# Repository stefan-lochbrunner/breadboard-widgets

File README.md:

A collection of widgets/adapters/breakouts to make prototyping easier.
For more infos please see [**project page on HaD.io**](https://hackaday.io/project/6332-breadboard-widgets). A panel with a subset of these booards can also be ordered from the [**DirtyPCBs store**](http://dirtypcbs.com/view.php?share=9791&accesskey=ab0e86ffb8323f031e5f15a2c98e4056)

#### ATtiny prog board
Programming board suitable for ATtiny45/85 microcontrollers. Plugs into a breadboards power rails to minimize required space.
USB version pin compatible with uUSB breakout.
[**more info**](https://hackaday.io/project/6332-breadboard-widgets/log/19613-attiny-prog-board)

##### Standard:

##### With USB:

#### DBx breakout
Simple breakout for DA-15, DB/DE-9 & DE-15(VGA) connectors. DB-9 to be placed on DA-15 footprint. [**more info**](https://hackaday.io/project/6332/log/26554)

#### ISP breakout
Simple ISP breakout. Order of pins corresponds to ATmega328 DIP so breakout can be plugged in next to it. Jumper wire required for RST. Also fits ATtiny45/85 with additional jumper for GND.
[**more info**](https://hackaday.io/project/6332-breadboard-widgets/log/19660-isp-breakout)

##### v1.2

Added two additional pins to ISP & breadboard headers to allow this board to be used as breakout for e.g. ESP-01's.

#### MOSFET breakout
DPAK MOSFET breakout to be used as single channel PWM driver. Footprint should also fit SOT-223 package where pin 2 is internally connected to tab.
[**more info**](https://hackaday.io/project/6332-breadboard-widgets/log/21781-mosfet-breakout-for-pwm-driver)

#### SMD LED breakout
Straight forward SMD LED breakout. See also [**revised button board that can be used as LED breakout**](https://github.com/stefan-lochbrunner/breadboard-widgets/tree/master/button)

##### single

##### multi

#### SOIC/TSSOP-16 breakout & protoboard
Some variations on a SOIC-16 and TSSOP-16 breakout board.

#### USB breakouts

##### uUSB breakout
Main functionality is to provide "VUSB circuitry" for AVR microcontrollers. Can also be used as generic uUSB breakout by shorting 68R resistor footprints or as breadboard power supply (supplying 5V).
[**more info**](https://hackaday.io/project/6332-breadboard-widgets/log/19615-uusb-breakout)

###### v1

###### v2
Allows for supplying different voltages by populating the bottom side with desired regulator. For 5V short solder jumper.

superseded by v3

###### v3
Allows for supplying different voltages by populating the bottom side with desired regulator. The following modes are possible:

- Supply rail and Vcc pin with 5V directly from USB (regulator not populated, short all 3 pads of solder jumper)
- Supply regulator with 5V from USB which in turn supplies rail and Vcc pin (short center and top pad)
- Supply regulator from rail and get regulated voltage on Vcc pin (short center and bottom pad)

##### USB-B

#### Audio breakouts
Breakout boards for 3.5mm TRS & RCA jacks. [**more info**](https://hackaday.io/project/6332-breadboard-widgets/log/21029-sufs-audio-breakouts)

Based on @sufzoli 's https://github.com/sufzoli/suf-electronics-breadboard

Combined both into single board to save PCB space.

#### Button w/ pull resistor
[**more info**](https://hackaday.io/project/6332-breadboard-widgets/log/19614-button-w-pull-updown)

##### single button
Small board that incorporates a button and pull-resistor. Can be plugged into power rails. Depending on which side of a breadboard it is plugged in, acts as pull-up or pull-down. Optional footprints for low-pass filter for debouncing.

##### single button with SMD LED breakout
added over complicated LED breakout to utilize board space. Also added arrow to indicate pull direction.

#### Negative voltage converter
Included files of @sufzoli 's [**voltage inverter**](https://github.com/sufzoli/suf-electronics-USB-INV-PM) here and remade in Eagle for coherency. [**more info**](https://hackaday.io/project/6332-breadboard-widgets/log/22127-sufs-negative-voltage-converter)

Based on ICL7660, inverts supply voltage.

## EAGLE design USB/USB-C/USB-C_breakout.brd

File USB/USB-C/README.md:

# USB 2.0 Type C breakout
-------------------------

USB-C breakout inspired by the [Adafruit USB Type C Breakout Board](https://github.com/adafruit/Adafruit-USB-C-Downstream-Breakout) with [breadboard power rail connector](https://hackaday.io/project/6332-breadboard-widgets/log/19631-pwr-thingy) and power indicator LED.

<br>

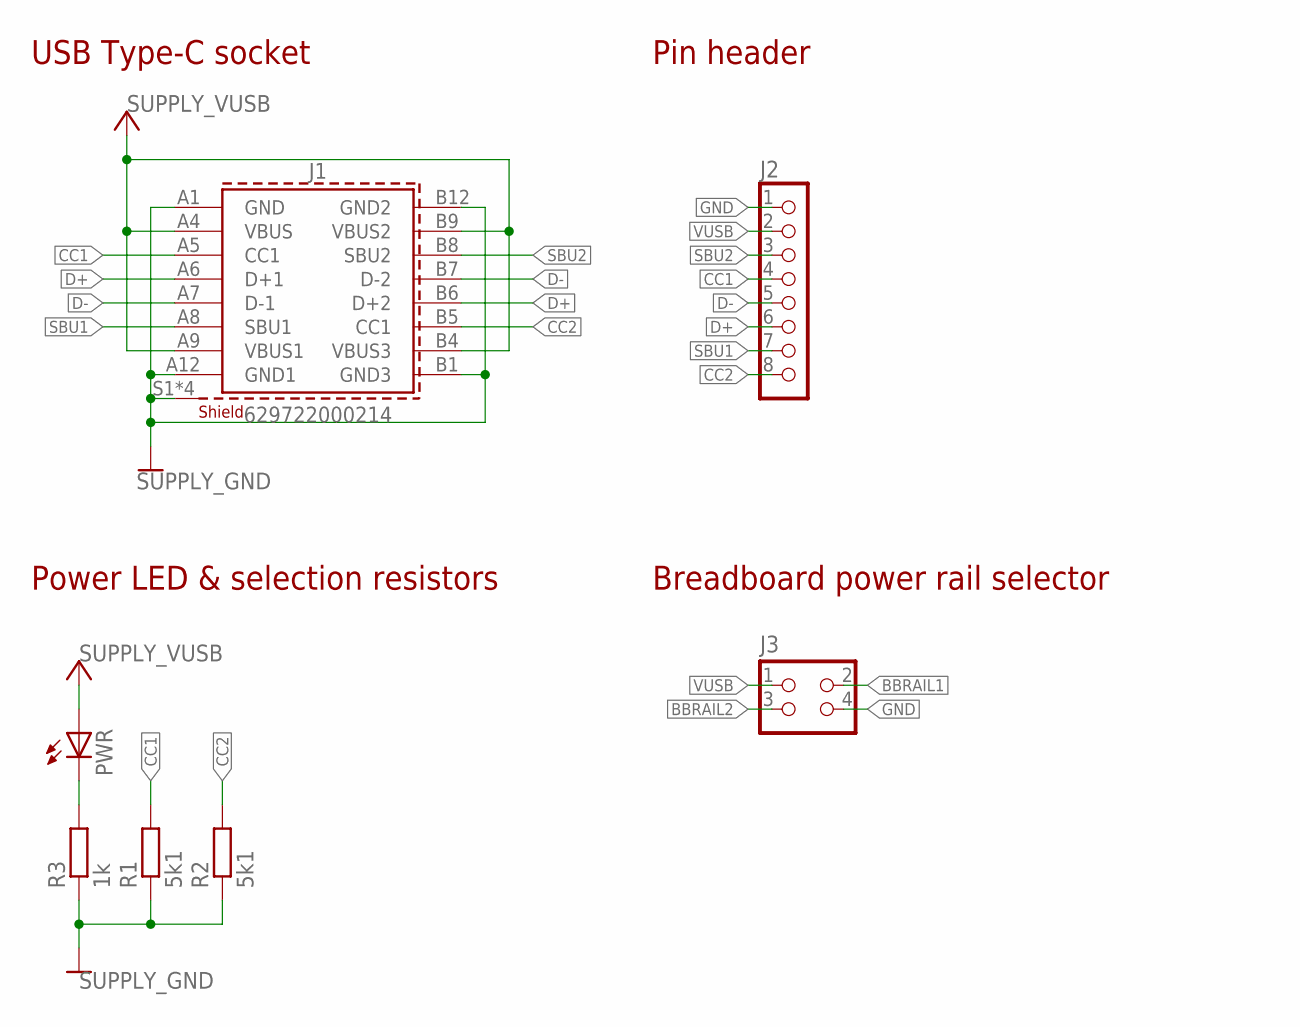
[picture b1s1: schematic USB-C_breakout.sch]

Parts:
J1: 629722000214
J2: CON_HEADER_1X08-PTH; M1X8
J3: CON_HEADER_2X02-PTH; M2X2
PWR: LED-0603; LED-603
R1, R2: 5k1; R603
R3: 1k; R603

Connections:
BBRAIL1: J3.2
BBRAIL2: J3.3
CC1: J1.A5 (CC1), J2.4, R1.2
CC2: J1.B5 (CC1), J2.8, R2.2
D+: J1.A6 (D+1), J1.B6 (D+2), J2.6
D-: J1.A7 (D-1), J1.B7 (D-2), J2.5
GND: J1.A1 (GND), J1.A12 (GND1), J1.B1 (GND3), J1.B12 (GND2), J1.S1 (SHIELD), J1.S2 (SHIELD), J1.S3 (SHIELD), J1.S4 (SHIELD), J2.1, J3.4, R1.1, R2.1, R3.1
unnamed: PWR.C, R3.2
SBU1: J1.A8 (SBU1), J2.7
SBU2: J1.B8 (SBU2), J2.3
VUSB: J1.A4 (VBUS), J1.A9 (VBUS1), J1.B4 (VBUS3), J1.B9 (VBUS2), J2.2, J3.1, PWR.A

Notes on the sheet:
USB Type-C socket
Pin header
Power LED & selection resistors
Breadboard power rail selector

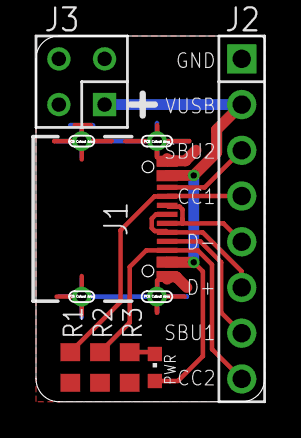
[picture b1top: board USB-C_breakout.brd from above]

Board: 2 copper layers, 12.7 x 20.3 mm, 7 parts (0 on the bottom side), 9 nets.

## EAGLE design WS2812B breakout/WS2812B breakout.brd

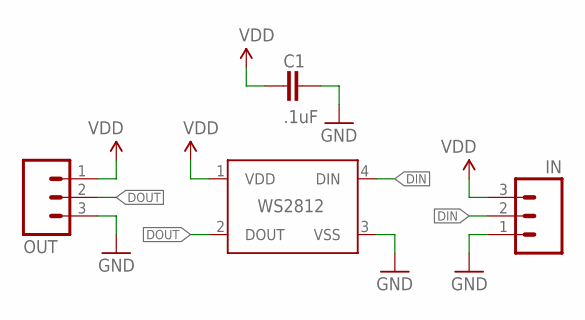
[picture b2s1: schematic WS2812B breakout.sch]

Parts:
C1: .1uF; C805
IN: CONN_03LOCK; 1X03_LOCK
OUT: CONN_03LOCK; 1X03_LOCK
WS2812: WS2812B

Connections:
DIN: IN.2, WS2812.4 (DIN)
DOUT: OUT.2, WS2812.2 (DOUT)
GND: C1.2, IN.1, OUT.3, WS2812.3 (VSS)
VDD: C1.1, IN.3, OUT.1, WS2812.1 (VDD)

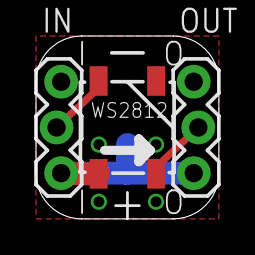
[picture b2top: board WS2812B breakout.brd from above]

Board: 2 copper layers, 10.2 x 10.2 mm, 4 parts (1 on the bottom side), 4 nets.

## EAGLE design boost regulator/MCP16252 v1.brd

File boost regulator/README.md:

Boost regulator board first designed by [**@sufzoli**](https://github.com/sufzoli), based on the [**Microchip MCP16252**](http://www.microchip.com/wwwproducts/en/MCP16252). [**more info**](https://hackaday.io/project/6332-breadboard-widgets/log/)

Set/remove jumper to output 3.3V/5V respectively.

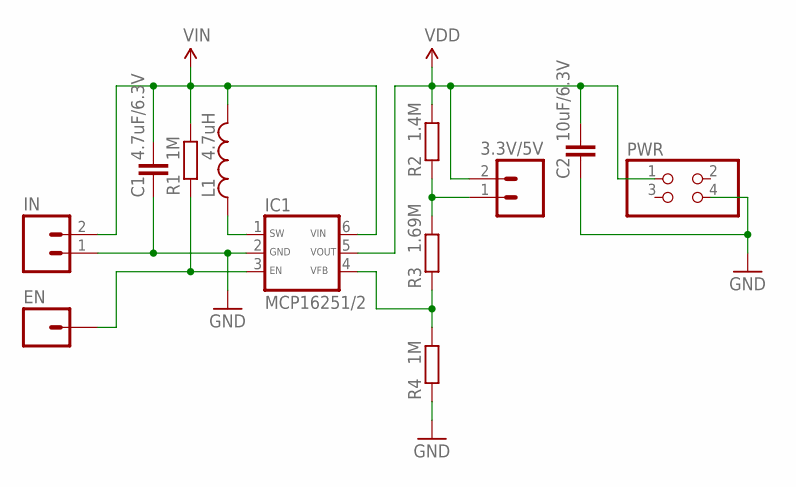
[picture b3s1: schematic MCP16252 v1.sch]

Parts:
3.3V/5V: M02PTH; 1X02
C1: 4.7uF/6.3V; C805
C2: 10uF/6.3V; C805
EN: M01PTH; 1X01
IC1: MCP16251/2; SOT-23-6
IN: M02PTH; 1X02
L1: 4.7uH; 1007
PWR: PINHD-2X2; 2X02
R1, R4: 1M; R603
R2: 1.4M; R603
R3: 1.69M; R603

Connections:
EN: EN.1, IC1.3 (EN), R1.1
GND: C1.2, C2.2, IC1.2 (GND), IN.1, PWR.4, R4.1
unnamed: IC1.1 (SW), L1.1
unnamed: IC1.4 (VFB), R3.1, R4.2
unnamed: 3.3V/5V.1, R2.1, R3.2
VDD: 3.3V/5V.2, C2.1, IC1.5 (VOUT), PWR.1, R2.2
VIN: C1.1, IC1.6 (VIN), IN.2, L1.2, R1.2

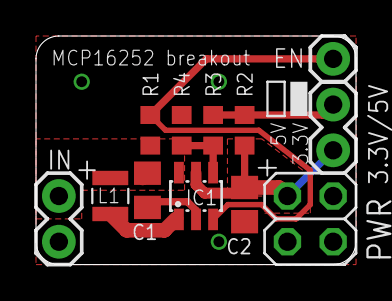
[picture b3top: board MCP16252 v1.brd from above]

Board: 2 copper layers, 17.8 x 12.7 mm, 12 parts (0 on the bottom side), 7 nets.

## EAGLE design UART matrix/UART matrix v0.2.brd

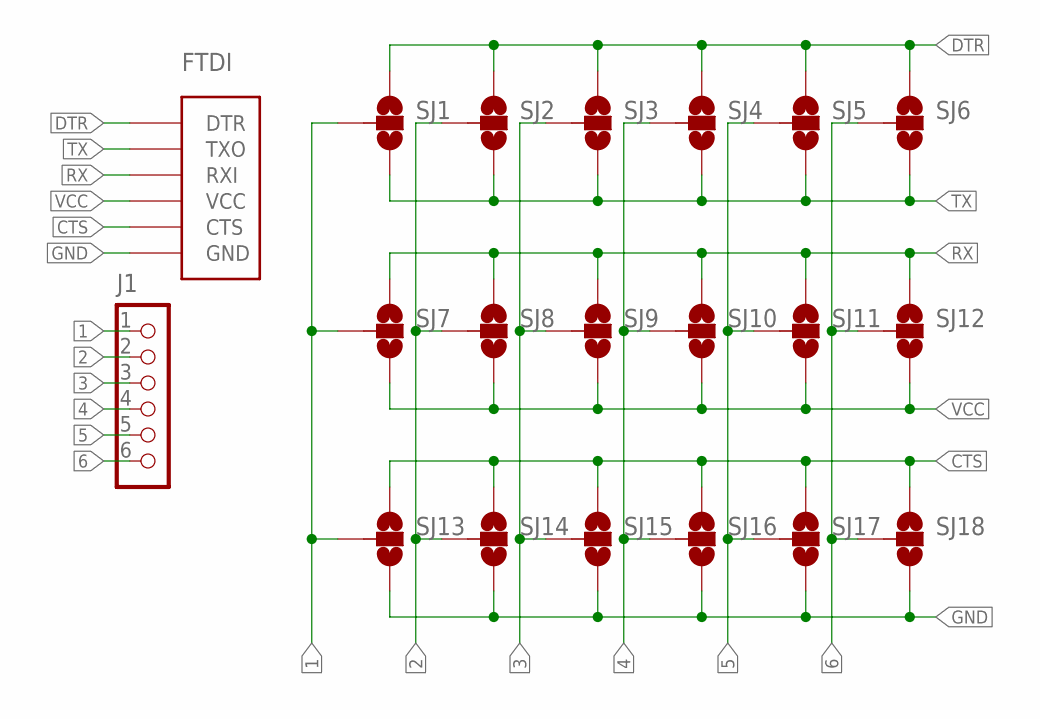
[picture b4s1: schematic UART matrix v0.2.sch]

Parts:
FTDI: FTDI_DEVICE; FTDI_DEVICE_SIDE
J1: CON_HEADER_1X06-PTH; M1X6
SJ1, SJ2, SJ3, SJ4, SJ5, SJ6, SJ7, SJ8, SJ9, SJ10, SJ11, SJ12, SJ13, SJ14, SJ15, SJ16, SJ17, SJ18: SOLDERJUMPER_2WAYT; SJ_2

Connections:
1: J1.1, SJ1.2, SJ7.2, SJ13.2
2: J1.2, SJ2.2, SJ8.2, SJ14.2
3: J1.3, SJ3.2, SJ9.2, SJ15.2
4: J1.4, SJ4.2, SJ10.2, SJ16.2
5: J1.5, SJ5.2, SJ11.2, SJ17.2
6: J1.6, SJ6.2, SJ12.2, SJ18.2
CTS: FTDI.P$5 (CTS), SJ13.1, SJ14.1, SJ15.1, SJ16.1, SJ17.1, SJ18.1
DTR: FTDI.P$1 (DTR), SJ1.1, SJ2.1, SJ3.1, SJ4.1, SJ5.1, SJ6.1
GND: FTDI.P$6 (GND), SJ13.3, SJ14.3, SJ15.3, SJ16.3, SJ17.3, SJ18.3
RX: FTDI.P$3 (RXI), SJ7.1, SJ8.1, SJ9.1, SJ10.1, SJ11.1, SJ12.1
TX: FTDI.P$2 (TXO), SJ1.3, SJ2.3, SJ3.3, SJ4.3, SJ5.3, SJ6.3
VCC: FTDI.P$4 (VCC), SJ7.3, SJ8.3, SJ9.3, SJ10.3, SJ11.3, SJ12.3

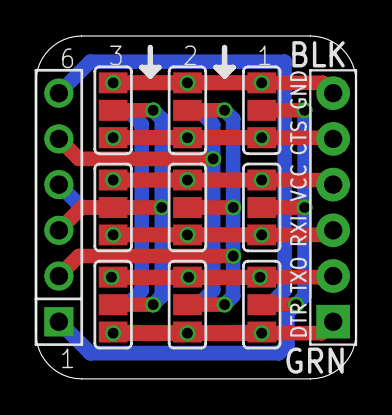
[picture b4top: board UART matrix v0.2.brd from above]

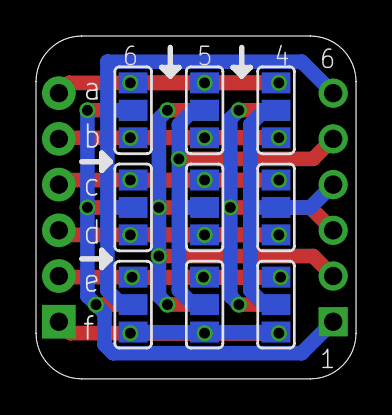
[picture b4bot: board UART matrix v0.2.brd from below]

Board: 2 copper layers, 17.8 x 19.1 mm, 20 parts (9 on the bottom side), 12 nets.

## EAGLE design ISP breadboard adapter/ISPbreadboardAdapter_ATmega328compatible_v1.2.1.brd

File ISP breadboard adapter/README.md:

Simple ISP breakout. Order of pins corresponds to ATmega328 DIP so breakout can be plugged in next to it. Jumper wire required for RST. Also fits ATtiny45/85 with additional jumper for GND.
[**more info**](https://hackaday.io/project/6332-breadboard-widgets/log/19660-isp-breakout)

**v1**

**v1.1**

**v1.2**

Added two additional pins to ISP & breadboard headers to allow this board to be used as breakout for e.g. ESP-01's.

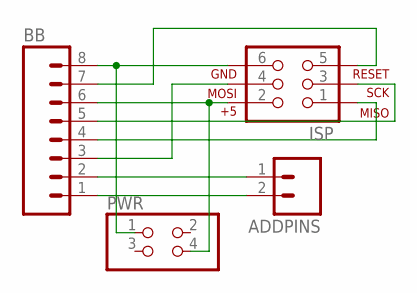
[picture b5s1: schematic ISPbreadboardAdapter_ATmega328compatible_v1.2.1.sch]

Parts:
ADDPINS: M02PTH; 1X02
BB: M08; 1X08_ROUND
ISP: AVR_SPI_PRG_6PTH; 2X3
PWR: PINHD-2X2; 2X02

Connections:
GND: BB.8, ISP.6, PWR.1
MISO: BB.4, ISP.1
MOSI: BB.3, ISP.4
unnamed: ADDPINS.1, BB.2
unnamed: ADDPINS.2, BB.1
RST: BB.7, ISP.5
SCK: BB.5, ISP.3
VCC: BB.6, ISP.2, PWR.4

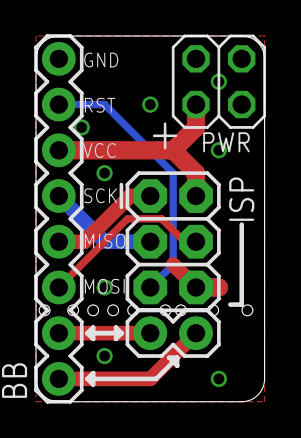
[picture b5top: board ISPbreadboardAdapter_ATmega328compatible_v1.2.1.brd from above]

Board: 2 copper layers, 12.7 x 20.3 mm, 4 parts (0 on the bottom side), 8 nets.

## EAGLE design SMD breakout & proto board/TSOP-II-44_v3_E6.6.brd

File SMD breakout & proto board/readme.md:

Some variations of SOIC/TSSOP-16 and -20 breakouts. [**more info**](https://hackaday.io/project/6332/log/26748)

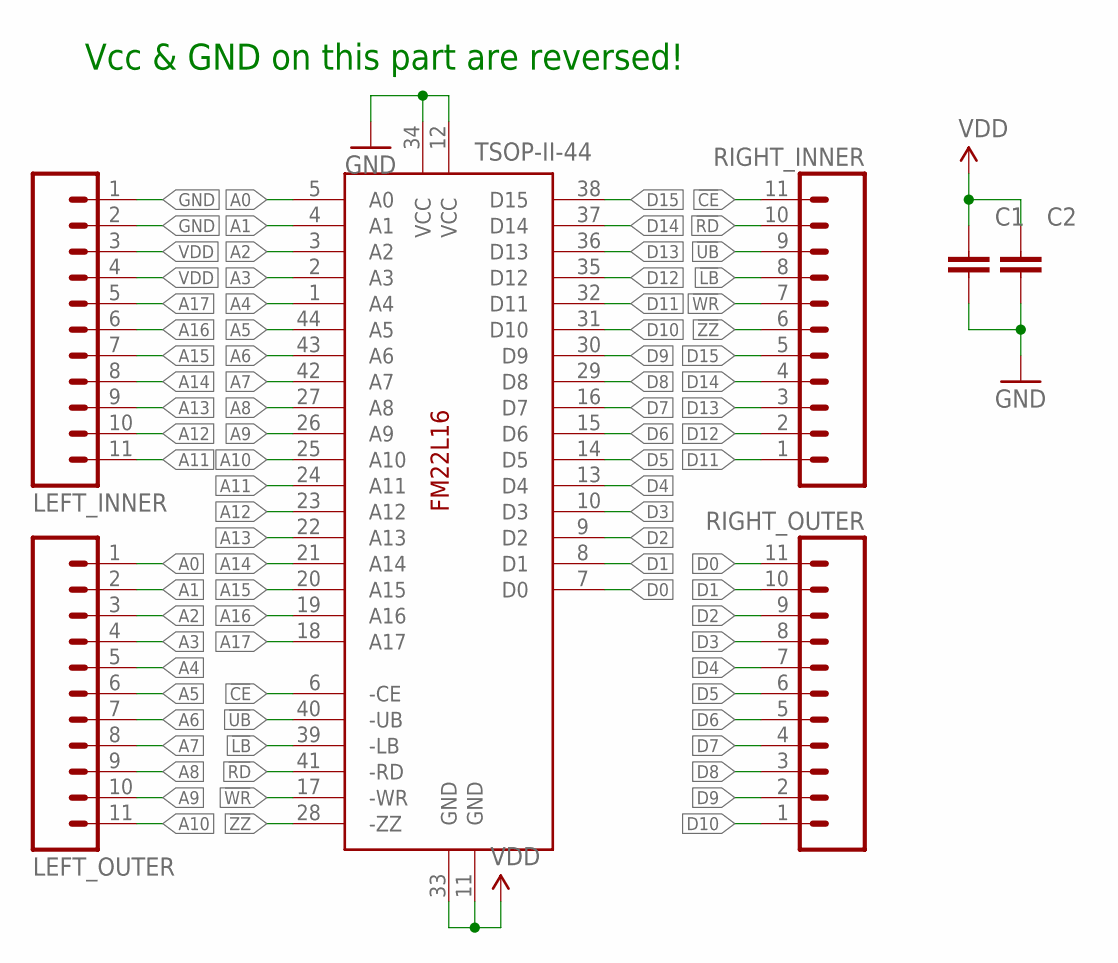
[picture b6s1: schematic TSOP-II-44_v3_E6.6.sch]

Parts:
C1, C2: CAPACITOR_NPOL-0603; C603
LEFT_INNER: M11PTH; 1X11
LEFT_OUTER: M11PTH; 1X11
RIGHT_INNER: M11PTH; 1X11
RIGHT_OUTER: M11PTH; 1X11
TSOP-II-44: FM22L16-TG; TSOPII-44

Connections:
!CE: RIGHT_INNER.11, TSOP-II-44.6 (-CE)
!LB: RIGHT_INNER.8, TSOP-II-44.39 (-LB)
!RD: RIGHT_INNER.10, TSOP-II-44.41 (-RD)
!UB: RIGHT_INNER.9, TSOP-II-44.40 (-UB)
!WR: RIGHT_INNER.7, TSOP-II-44.17 (-WR)
!ZZ: RIGHT_INNER.6, TSOP-II-44.28 (-ZZ)
A0: LEFT_OUTER.1, TSOP-II-44.5 (A0)
A1: LEFT_OUTER.2, TSOP-II-44.4 (A1)
A2: LEFT_OUTER.3, TSOP-II-44.3 (A2)
A3: LEFT_OUTER.4, TSOP-II-44.2 (A3)
A4: LEFT_OUTER.5, TSOP-II-44.1 (A4)
A5: LEFT_OUTER.6, TSOP-II-44.44 (A5)
A6: LEFT_OUTER.7, TSOP-II-44.43 (A6)
A7: LEFT_OUTER.8, TSOP-II-44.42 (A7)
A8: LEFT_OUTER.9, TSOP-II-44.27 (A8)
A9: LEFT_OUTER.10, TSOP-II-44.26 (A9)
A10: LEFT_OUTER.11, TSOP-II-44.25 (A10)
A11: LEFT_INNER.11, TSOP-II-44.24 (A11)
A12: LEFT_INNER.10, TSOP-II-44.23 (A12)
A13: LEFT_INNER.9, TSOP-II-44.22 (A13)
A14: LEFT_INNER.8, TSOP-II-44.21 (A14)
A15: LEFT_INNER.7, TSOP-II-44.20 (A15)
A16: LEFT_INNER.6, TSOP-II-44.19 (A16)
A17: LEFT_INNER.5, TSOP-II-44.18 (A17)
D0: RIGHT_OUTER.11, TSOP-II-44.7 (D0)
D1: RIGHT_OUTER.10, TSOP-II-44.8 (D1)
D2: RIGHT_OUTER.9, TSOP-II-44.9 (D2)
D3: RIGHT_OUTER.8, TSOP-II-44.10 (D3)
D4: RIGHT_OUTER.7, TSOP-II-44.13 (D4)
D5: RIGHT_OUTER.6, TSOP-II-44.14 (D5)
D6: RIGHT_OUTER.5, TSOP-II-44.15 (D6)
D7: RIGHT_OUTER.4, TSOP-II-44.16 (D7)
D8: RIGHT_OUTER.3, TSOP-II-44.29 (D8)
D9: RIGHT_OUTER.2, TSOP-II-44.30 (D9)
D10: RIGHT_OUTER.1, TSOP-II-44.31 (D10)
D11: RIGHT_INNER.1, TSOP-II-44.32 (D11)
D12: RIGHT_INNER.2, TSOP-II-44.35 (D12)
D13: RIGHT_INNER.3, TSOP-II-44.36 (D13)
D14: RIGHT_INNER.4, TSOP-II-44.37 (D14)
D15: RIGHT_INNER.5, TSOP-II-44.38 (D15)
GND: C1.2, C2.2, LEFT_INNER.1, LEFT_INNER.2, TSOP-II-44.12 (VCC), TSOP-II-44.34 (VCC)
VDD: C1.1, C2.1, LEFT_INNER.3, LEFT_INNER.4, TSOP-II-44.11 (GND), TSOP-II-44.33 (GND)

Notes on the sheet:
Vcc & GND on this part are reversed!

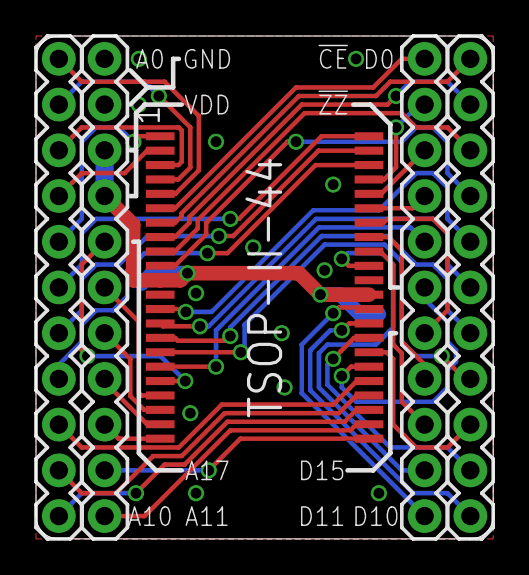
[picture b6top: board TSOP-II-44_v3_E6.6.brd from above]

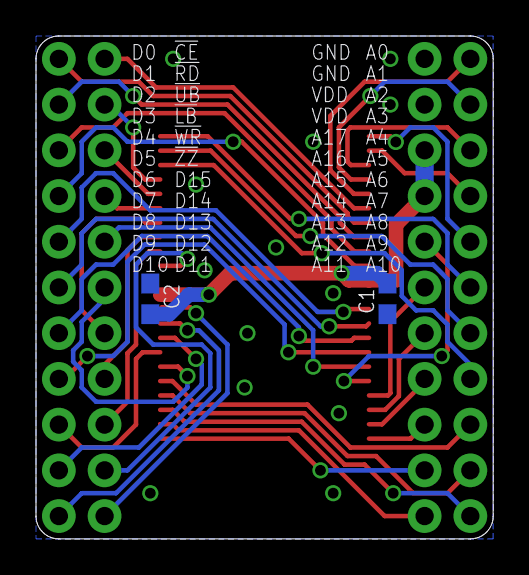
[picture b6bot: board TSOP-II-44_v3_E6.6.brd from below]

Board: 2 copper layers, 25.4 x 27.9 mm, 7 parts (2 on the bottom side), 42 nets.

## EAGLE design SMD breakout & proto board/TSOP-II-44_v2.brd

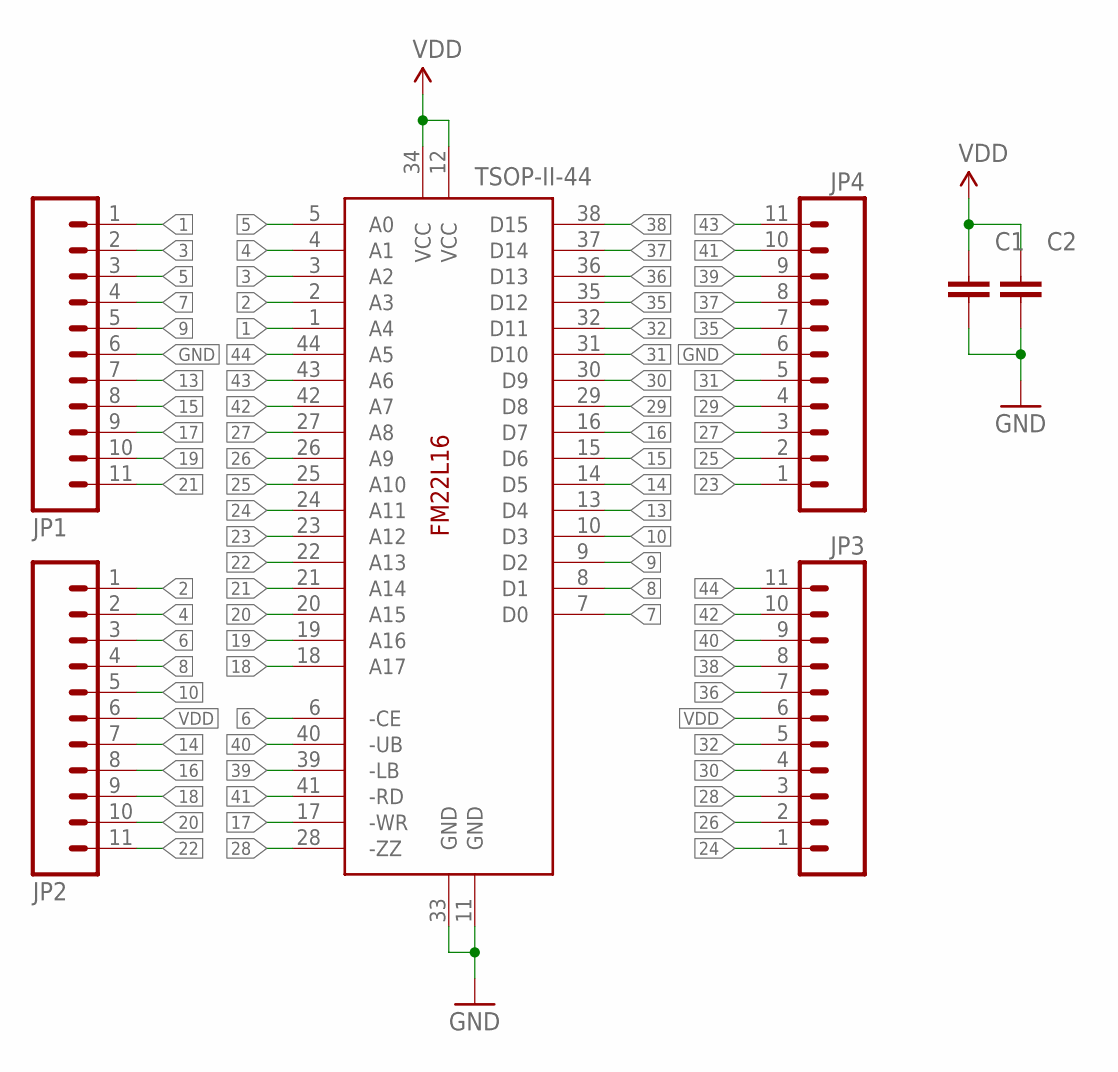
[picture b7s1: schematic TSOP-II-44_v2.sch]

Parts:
C1, C2: CAPACITOR_NPOL-0603; C603
JP1, JP2, JP3, JP4: M11PTH; 1X11
TSOP-II-44: FM22L16-TG; TSOPII-44

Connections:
1: JP1.1, TSOP-II-44.1 (A4)
2: JP2.1, TSOP-II-44.2 (A3)
3: JP1.2, TSOP-II-44.3 (A2)
4: JP2.2, TSOP-II-44.4 (A1)
5: JP1.3, TSOP-II-44.5 (A0)
6: JP2.3, TSOP-II-44.6 (-CE)
7: JP1.4, TSOP-II-44.7 (D0)
8: JP2.4, TSOP-II-44.8 (D1)
9: JP1.5, TSOP-II-44.9 (D2)
10: JP2.5, TSOP-II-44.10 (D3)
13: JP1.7, TSOP-II-44.13 (D4)
14: JP2.7, TSOP-II-44.14 (D5)
15: JP1.8, TSOP-II-44.15 (D6)
16: JP2.8, TSOP-II-44.16 (D7)
17: JP1.9, TSOP-II-44.17 (-WR)
18: JP2.9, TSOP-II-44.18 (A17)
19: JP1.10, TSOP-II-44.19 (A16)
20: JP2.10, TSOP-II-44.20 (A15)
21: JP1.11, TSOP-II-44.21 (A14)
22: JP2.11, TSOP-II-44.22 (A13)
23: JP4.1, TSOP-II-44.23 (A12)
24: JP3.1, TSOP-II-44.24 (A11)
25: JP4.2, TSOP-II-44.25 (A10)
26: JP3.2, TSOP-II-44.26 (A9)
27: JP4.3, TSOP-II-44.27 (A8)
28: JP3.3, TSOP-II-44.28 (-ZZ)
29: JP4.4, TSOP-II-44.29 (D8)
30: JP3.4, TSOP-II-44.30 (D9)
31: JP4.5, TSOP-II-44.31 (D10)
32: JP3.5, TSOP-II-44.32 (D11)
35: JP4.7, TSOP-II-44.35 (D12)
36: JP3.7, TSOP-II-44.36 (D13)
37: JP4.8, TSOP-II-44.37 (D14)
38: JP3.8, TSOP-II-44.38 (D15)
39: JP4.9, TSOP-II-44.39 (-LB)
40: JP3.9, TSOP-II-44.40 (-UB)
41: JP4.10, TSOP-II-44.41 (-RD)
42: JP3.10, TSOP-II-44.42 (A7)
43: JP4.11, TSOP-II-44.43 (A6)
44: JP3.11, TSOP-II-44.44 (A5)
GND: C1.2, C2.2, JP1.6, JP4.6, TSOP-II-44.11 (GND), TSOP-II-44.33 (GND)
VDD: C1.1, C2.1, JP2.6, JP3.6, TSOP-II-44.12 (VCC), TSOP-II-44.34 (VCC)

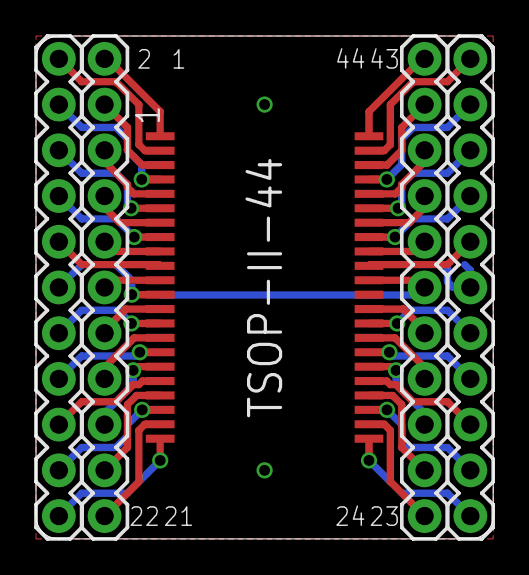
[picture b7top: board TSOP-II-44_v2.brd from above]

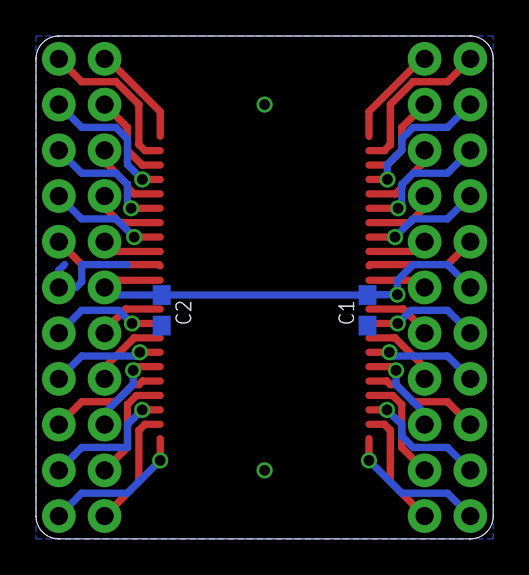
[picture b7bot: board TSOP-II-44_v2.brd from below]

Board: 2 copper layers, 25.4 x 27.9 mm, 7 parts (2 on the bottom side), 42 nets.

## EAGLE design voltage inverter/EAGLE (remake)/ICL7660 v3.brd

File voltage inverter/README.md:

Included @sufzoli 's [**voltage inverter**](https://github.com/sufzoli/suf-electronics-USB-INV-PM) here and remade in Eagle for coherency. [**more info**](https://hackaday.io/project/6332-breadboard-widgets/log/22127-sufs-negative-voltage-converter)

Based on ICL7660, inverts supply voltage.

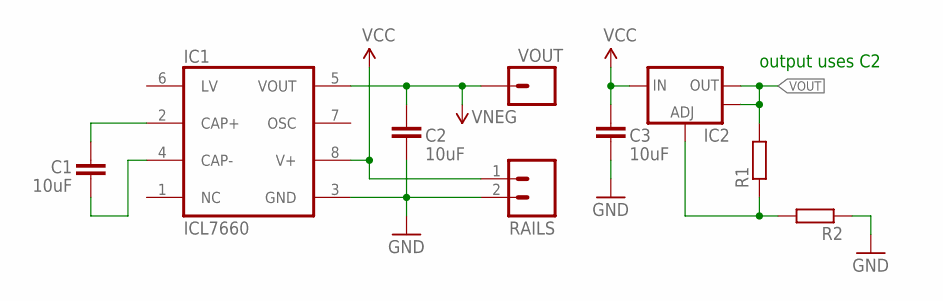
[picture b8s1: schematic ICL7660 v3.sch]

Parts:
C1, C2: 10uF; C1206
C3: 10uF; C805
IC1: ICL7660; SO08
IC2: V_REG_LM1117SOT223; SOT223
R1, R2: RESISTORR805-0805; R805
RAILS: M02PTH; 1X02
VOUT: M01PTH; 1X01

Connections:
GND: C2.2, C3.2, IC1.3 (GND), R2.1, RAILS.2
unnamed: C1.2, IC1.2 (CAP+)
unnamed: C1.1, IC1.4 (CAP-)
unnamed: IC2.1 (ADJ), R1.1, R2.2
VCC: C3.1, IC1.8 (V+), IC2.3 (IN), RAILS.1
VOUT: C2.1, IC1.5 (VOUT), IC2.2 (OUT), IC2.4 (OUT), R1.2, VOUT.1

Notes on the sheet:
output uses C2

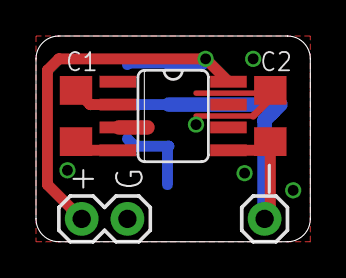
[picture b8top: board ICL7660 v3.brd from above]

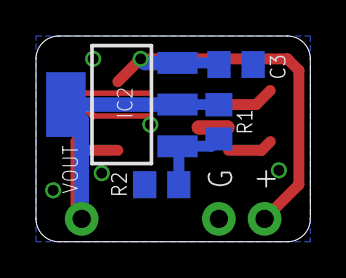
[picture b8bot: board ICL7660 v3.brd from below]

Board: 2 copper layers, 15.2 x 11.4 mm, 9 parts (4 on the bottom side), 6 nets.

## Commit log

2015-05-23 :neckbeard: Added .gitattributes & .gitignore files
2015-05-23 Added ATtiny programming board
2015-05-23 added button w/ pull-resistor
2015-05-23 added uUSB breakout
2015-05-23 added prog board readme
2015-05-23 added readme
2015-06-16 updated project link in readme
2015-06-16 added ISPbreadboardAdapter
2015-06-17 updated readme w/ images
2015-06-20 added some info to silk screen
2015-06-20 updated images of brd files
2015-06-21 added single_button-dual_LED
2015-06-21 updated sch.png
2015-06-23 updated .brd
2015-06-23 added SMD LED breakout
2015-06-24 added uUSB breakout v3 to replace v2
2015-06-24 removed uUSB breakout v2
2015-07-16 merged @sufzoli 's suf-electronics-breadboard repo & restructured content
2015-07-16 added images
2015-07-29 added multi LED and MOSFET breakout
2015-07-29 changed file names
2015-08-04 added voltage inverter
2015-08-04 updated brd & images
2015-10-09 added DBx breakout
2015-10-12 updated board
2015-10-12 updated brd
2015-10-12 updated images
2015-10-18 added SMD breakout & proto board
2015-10-18 renamed boards image
2015-11-05 added ISP breakout v1.1
2015-11-15 added ISBbreadboardAdapter v1.2
2015-12-11 updated ATtiny prog board with USB
2015-12-11 updated brd image
2016-01-05 added ICL7669 v3
2016-01-06 added SOIC_TSSOP-20 boards
2016-01-20 added TSOP-II-44 breakout
2016-01-20 added TSOP-II-44_v2 with minor changes
2016-01-21 added TSOP-II-44_v3 with SRAM pinout
2016-01-22 test
2016-01-23 swapped supply pins
2016-01-24 added ISP breakout v1.2.1
2016-01-24 added UART matrix
2016-07-31 added MCP16252 boost regulator board
2016-10-09 added prog board BOM
2016-10-09 updated prog board BOM
2016-10-09 added boost regulator BOM
2016-10-09 updated boost regulator BOM
2016-10-09 added button BOM
2016-10-09 updated button BOM
2016-10-09 added more BOMs
2022-07-19 Added WS2812B breakout
2022-12-12 Added USB-C 2.0 breakout
2022-12-12 Updated ATtiny prog board README.md.
2022-12-12 Updated uUSB breakout README.md
2022-12-12 Added USB-C breakout README.md
2022-12-12 Updated ATtiny prog board README.md
2022-12-12 Updated USB-C breakout README.md
2022-12-12 Updated ISP breadboard adapter README.md
2022-12-12 Updated SMD LED breakout README.md

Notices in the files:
parts and their libraries:
SparkFun-Connectors: Licensing: CC v3.0 Share-Alike You are welcome to use this library for commercial purposes.
SparkFun-Connectors: Licensing: Creative Commons ShareAlike 4.0 International - https://creativecommons.org/licenses/by-sa/4.0
Wurth_Connectors_WR-USB: Copyright: Würth Elektronik
